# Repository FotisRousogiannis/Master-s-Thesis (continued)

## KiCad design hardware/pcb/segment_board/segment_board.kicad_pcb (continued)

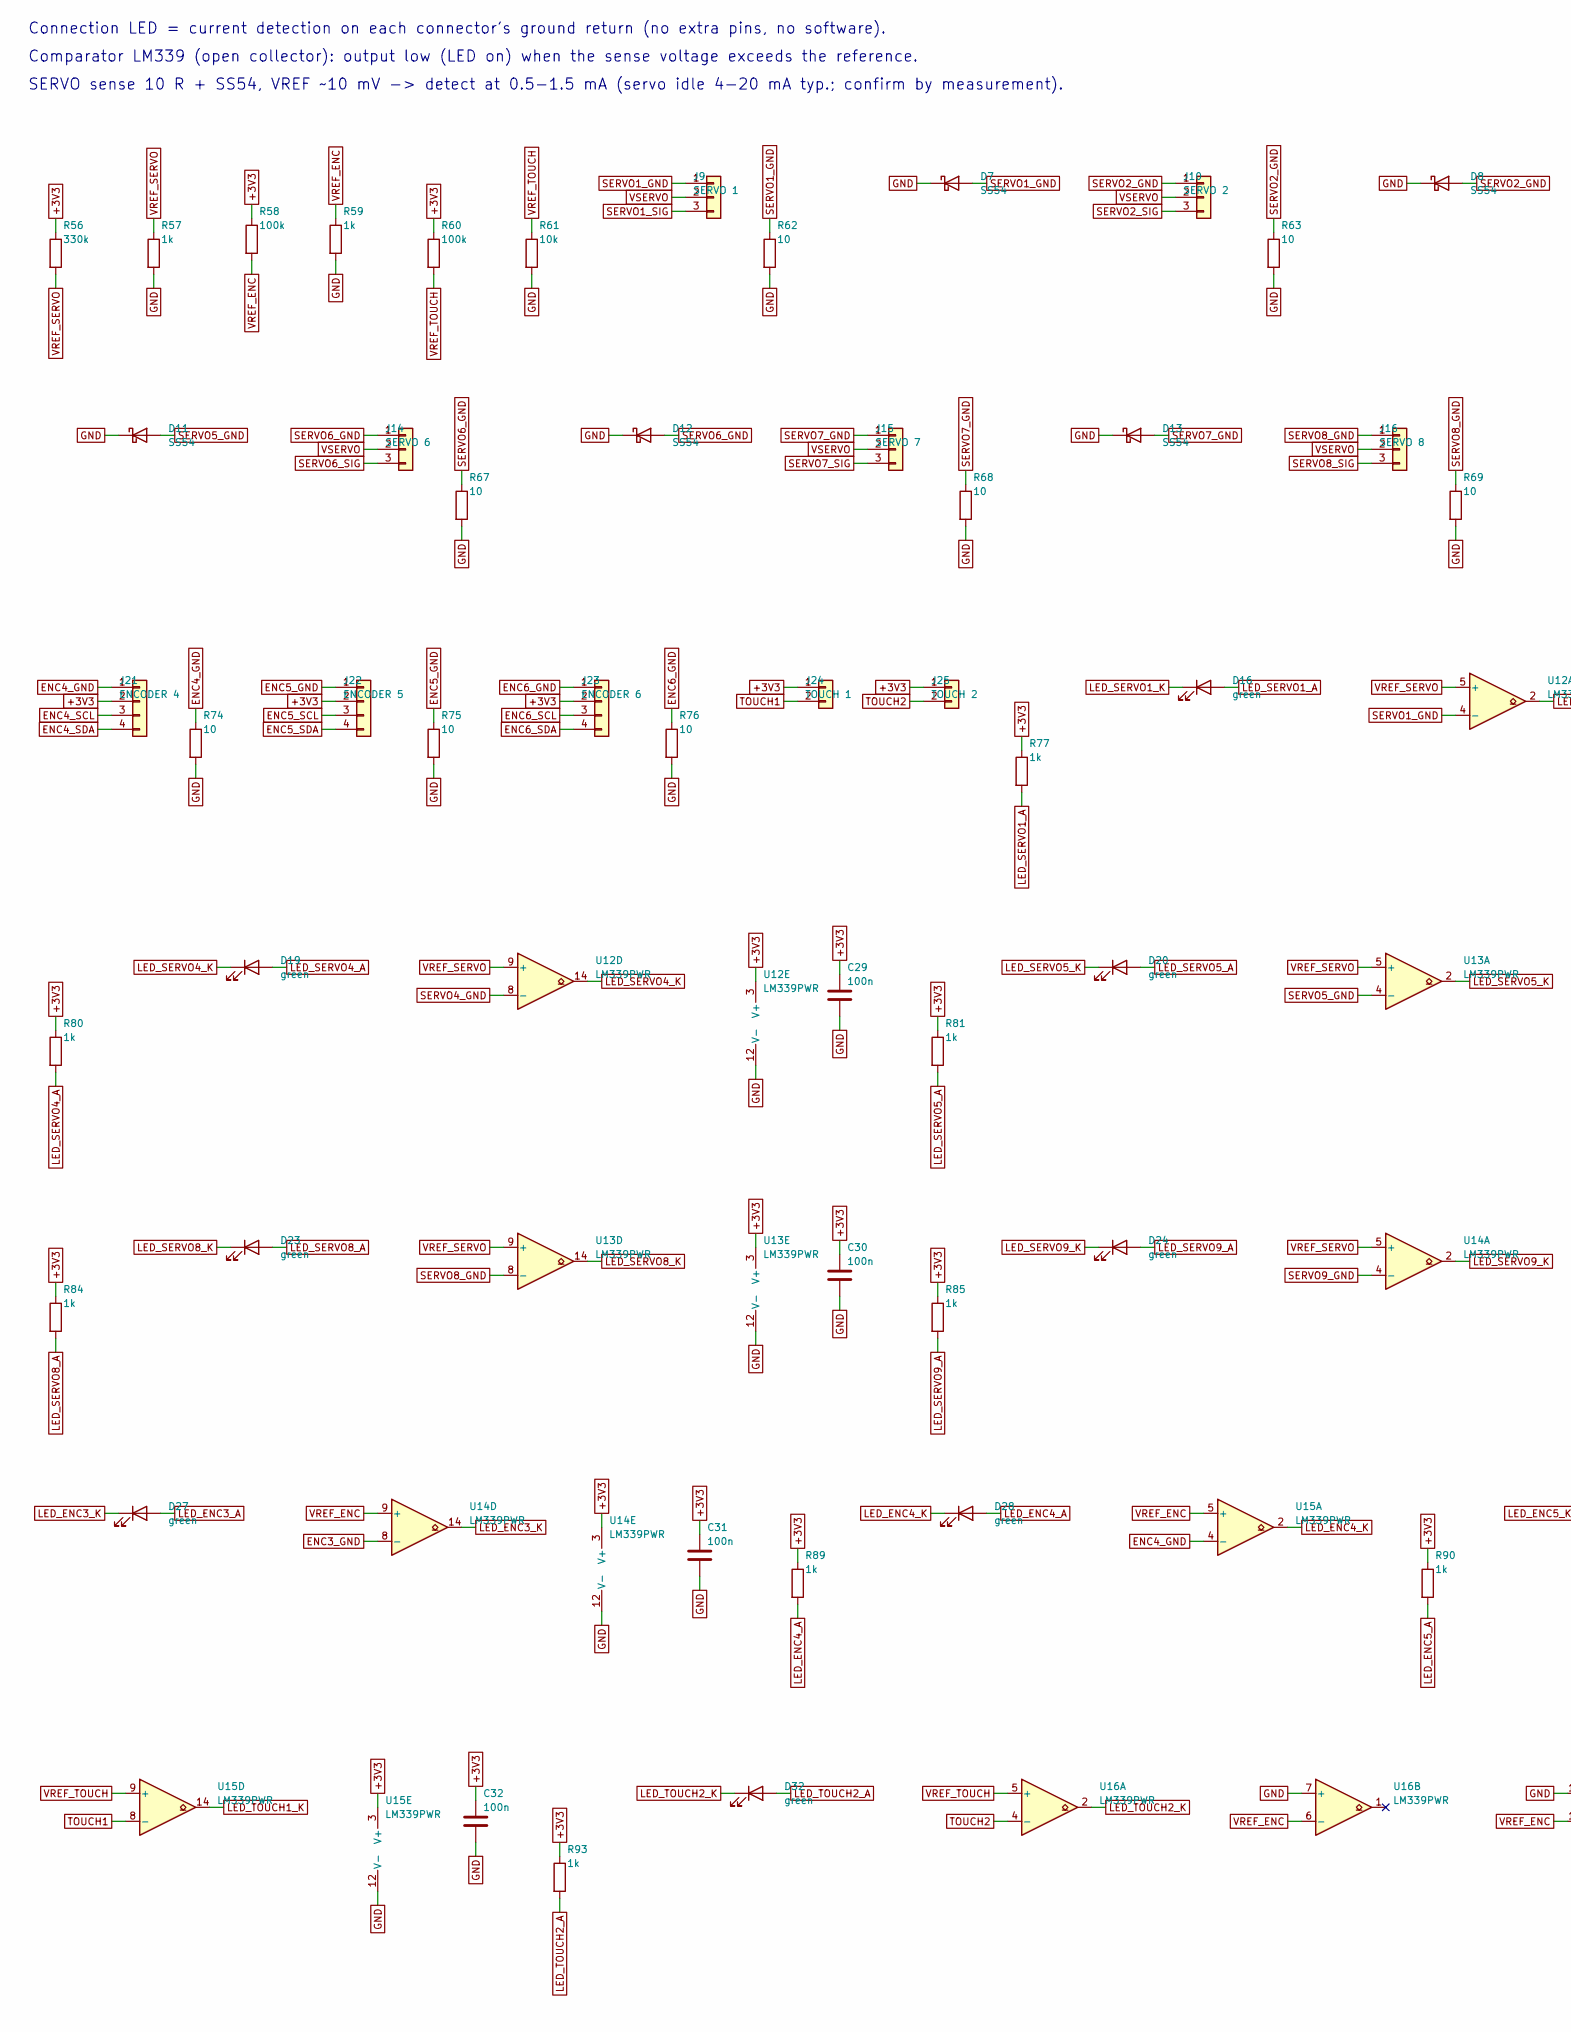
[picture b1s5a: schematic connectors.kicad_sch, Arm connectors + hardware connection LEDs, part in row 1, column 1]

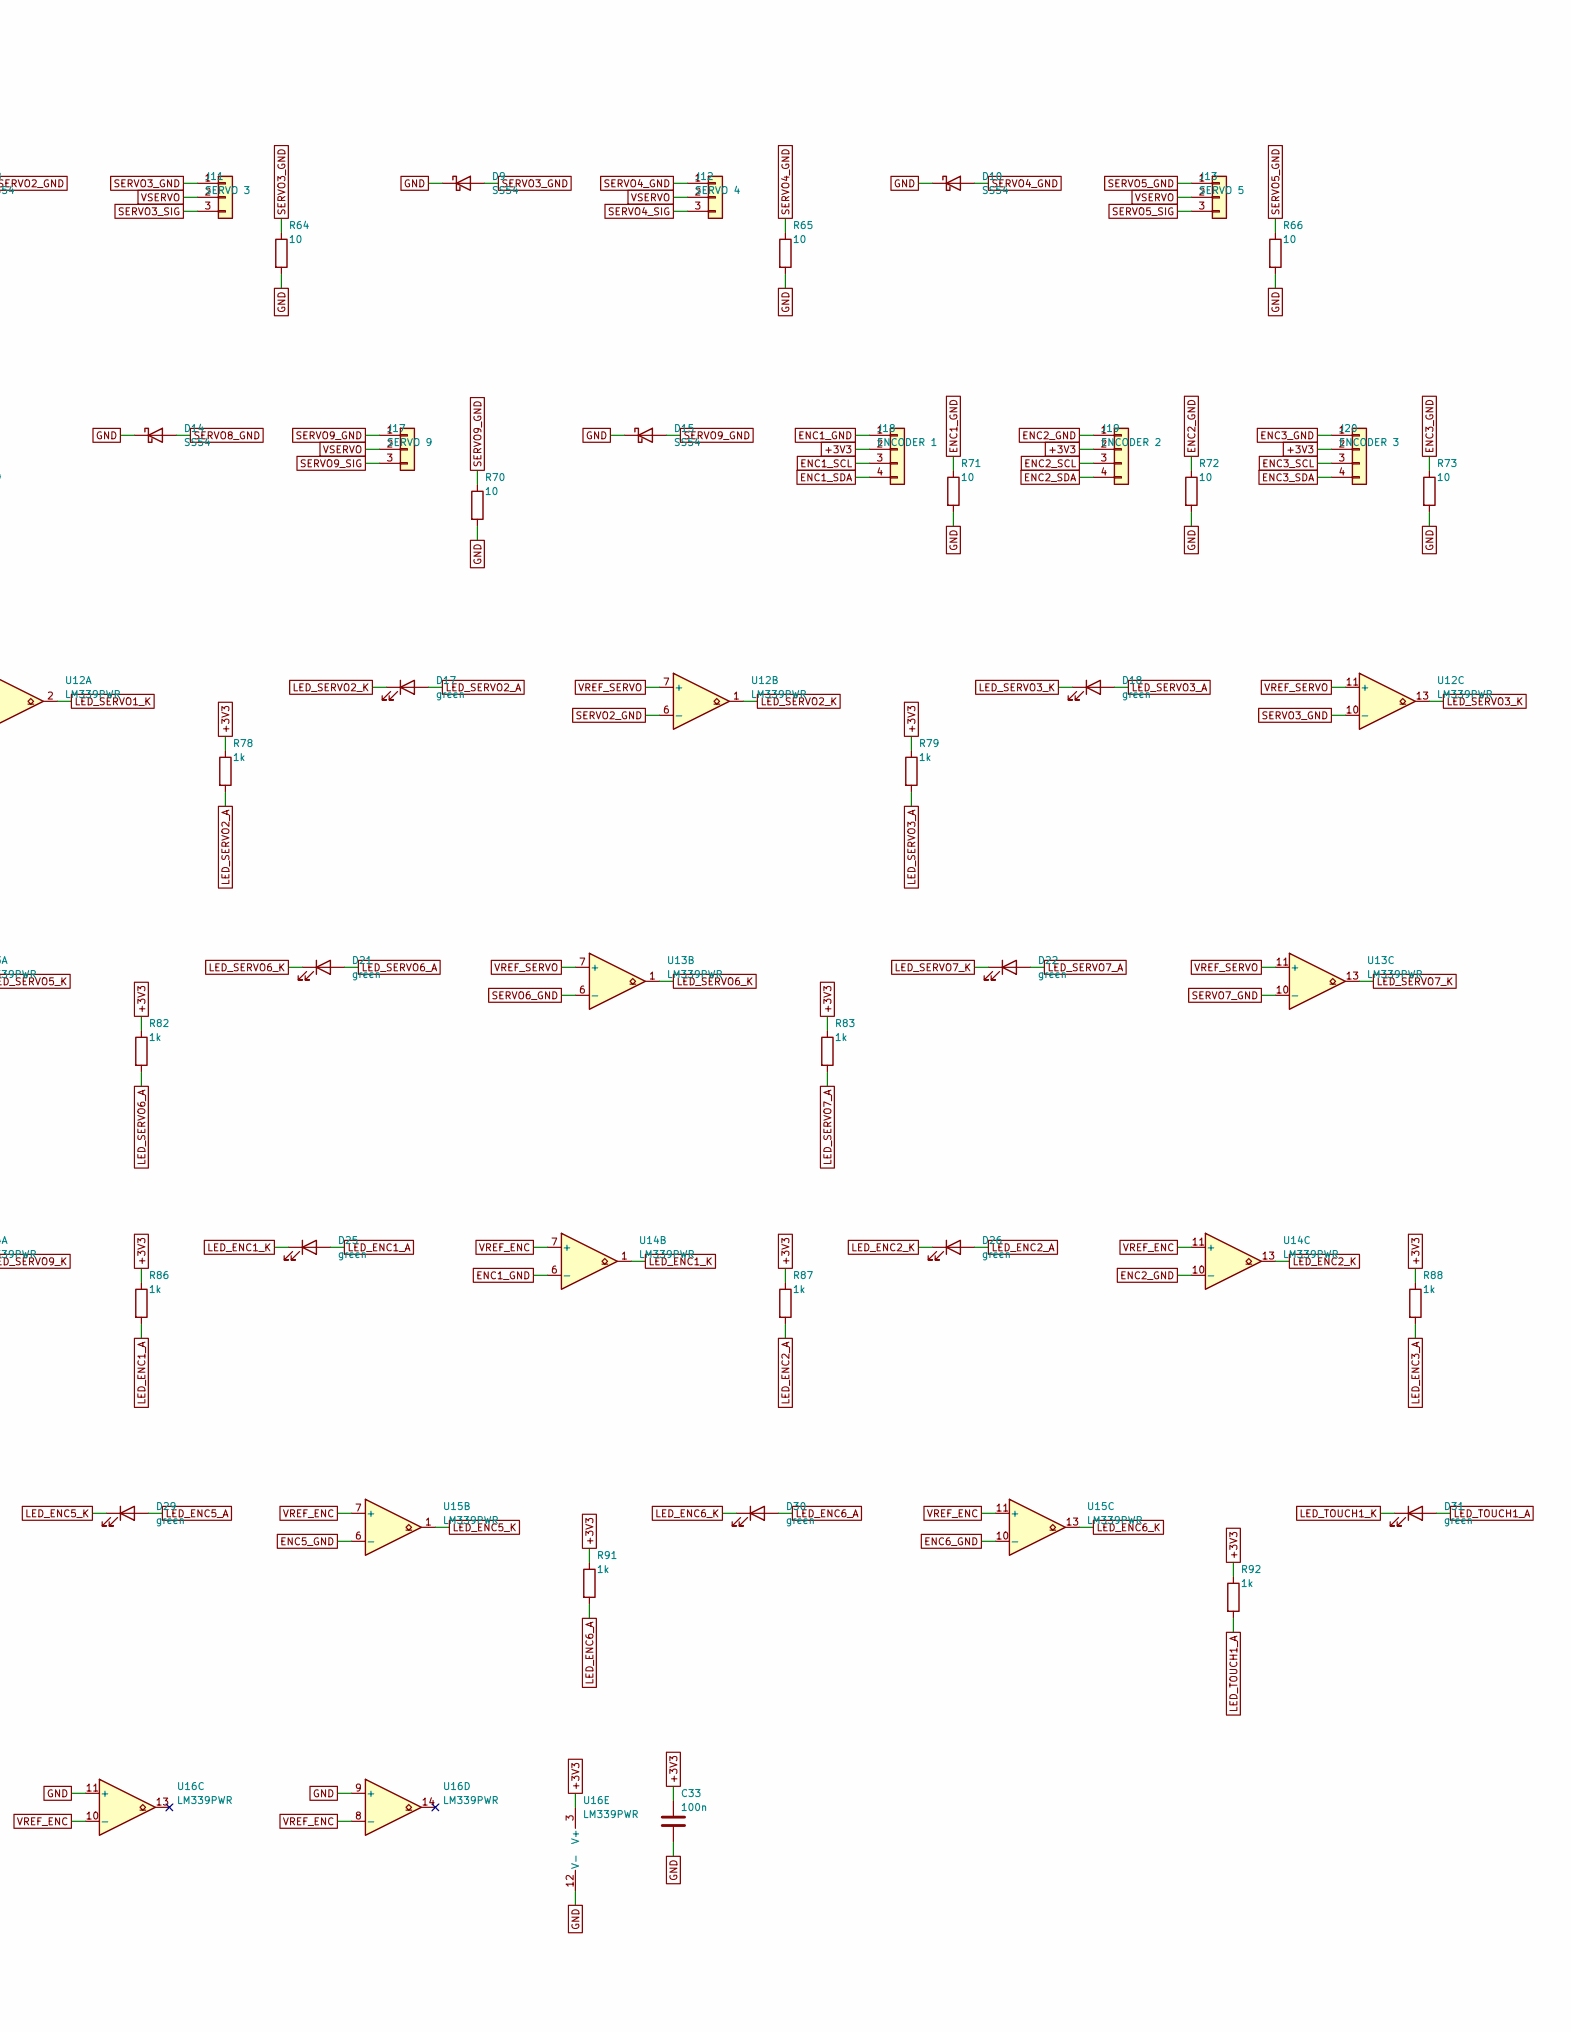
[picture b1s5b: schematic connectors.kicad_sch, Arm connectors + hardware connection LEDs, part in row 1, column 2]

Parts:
C29, C30, C31, C32, C33: 100n; C_0402_1005Metric; LCSC C1525
D7, D8, D9, D10, D11, D12, D13, D14, D15: SS54; D_SMA; LCSC C22452
D16, D17, D18, D19, D20, D21, D22, D23, D24, D25, D26, D27, D28, D29, D30, D31, D32: green; LED_0603_1608Metric; LCSC C2986030
J9: SERVO 1; PhoenixContact_MCV_1,5_3-G-3.5_1x03_P3.50mm_Vertical
J10: SERVO 2; PhoenixContact_MCV_1,5_3-G-3.5_1x03_P3.50mm_Vertical
J11: SERVO 3; PhoenixContact_MCV_1,5_3-G-3.5_1x03_P3.50mm_Vertical
J12: SERVO 4; PhoenixContact_MCV_1,5_3-G-3.5_1x03_P3.50mm_Vertical
J13: SERVO 5; PhoenixContact_MCV_1,5_3-G-3.5_1x03_P3.50mm_Vertical
J14: SERVO 6; PhoenixContact_MCV_1,5_3-G-3.5_1x03_P3.50mm_Vertical
J15: SERVO 7; PhoenixContact_MCV_1,5_3-G-3.5_1x03_P3.50mm_Vertical
J16: SERVO 8; PhoenixContact_MCV_1,5_3-G-3.5_1x03_P3.50mm_Vertical
J17: SERVO 9; PhoenixContact_MCV_1,5_3-G-3.5_1x03_P3.50mm_Vertical
J18: ENCODER 1; PhoenixContact_MCV_1,5_4-G-3.5_1x04_P3.50mm_Vertical
J19: ENCODER 2; PhoenixContact_MCV_1,5_4-G-3.5_1x04_P3.50mm_Vertical
J20: ENCODER 3; PhoenixContact_MCV_1,5_4-G-3.5_1x04_P3.50mm_Vertical
J21: ENCODER 4; PhoenixContact_MCV_1,5_4-G-3.5_1x04_P3.50mm_Vertical
J22: ENCODER 5; PhoenixContact_MCV_1,5_4-G-3.5_1x04_P3.50mm_Vertical
J23: ENCODER 6; PhoenixContact_MCV_1,5_4-G-3.5_1x04_P3.50mm_Vertical
J24: TOUCH 1; PhoenixContact_MCV_1,5_2-G-3.5_1x02_P3.50mm_Vertical
J25: TOUCH 2; PhoenixContact_MCV_1,5_2-G-3.5_1x02_P3.50mm_Vertical
R56: 330k; R_0402_1005Metric; LCSC C25778
R57, R59, R77, R78, R79, R80, R81, R82, R83, R84, R85, R86, R87, R88, R89, R90, R91, R92, R93: 1k; R_0402_1005Metric; LCSC C11702
R58, R60: 100k; R_0402_1005Metric; LCSC C25741
R61: 10k; R_0402_1005Metric; LCSC C25744
R62, R63, R64, R65, R66, R67, R68, R69, R70, R71, R72, R73, R74, R75, R76: 10; R_0402_1005Metric; LCSC C25077
U12, U13, U14, U15, U16: LM339PWR; TSSOP-14_4.4x5mm_P0.65mm; LCSC C42184

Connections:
+3V3: C29.1, C30.1, C31.1, C32.1, C33.1, J18.2, J19.2, J20.2, J21.2, J22.2, J23.2, J24.1, J25.1, R56.1, R58.1, R60.1, R77.1, R78.1, R79.1, R80.1, R81.1, R82.1, R83.1, R84.1, R85.1, R86.1, R87.1, R88.1, R89.1, R90.1, R91.1, R92.1, R93.1, U12.3 (V+), U13.3 (V+), U14.3 (V+), U15.3 (V+), U16.3 (V+); also elsewhere on the board
ENC1_GND: J18.1, R71.1, U14.6 (-)
ENC1_SCL: J18.3; also elsewhere on the board
ENC1_SDA: J18.4; also elsewhere on the board
ENC2_GND: J19.1, R72.1, U14.10 (-)
ENC2_SCL: J19.3; also elsewhere on the board
ENC2_SDA: J19.4; also elsewhere on the board
ENC3_GND: J20.1, R73.1, U14.8 (-)
ENC3_SCL: J20.3; also elsewhere on the board
ENC3_SDA: J20.4; also elsewhere on the board
ENC4_GND: J21.1, R74.1, U15.4 (-)
ENC4_SCL: J21.3; also elsewhere on the board
ENC4_SDA: J21.4; also elsewhere on the board
ENC5_GND: J22.1, R75.1, U15.6 (-)
ENC5_SCL: J22.3; also elsewhere on the board
ENC5_SDA: J22.4; also elsewhere on the board
ENC6_GND: J23.1, R76.1, U15.10 (-)
ENC6_SCL: J23.3; also elsewhere on the board
ENC6_SDA: J23.4; also elsewhere on the board
GND: C29.2, C30.2, C31.2, C32.2, C33.2, D7.1 (K), D8.1 (K), D9.1 (K), D10.1 (K), D11.1 (K), D12.1 (K), D13.1 (K), D14.1 (K), D15.1 (K), R57.2, R59.2, R61.2, R62.2, R63.2, R64.2, R65.2, R66.2, R67.2, R68.2, R69.2, R70.2, R71.2, R72.2, R73.2, R74.2, R75.2, R76.2, U12.12 (V-), U13.12 (V-), U14.12 (V-), U15.12 (V-), U16.7 (+), U16.9 (+), U16.11 (+), U16.12 (V-); also elsewhere on the board
LED_ENC1_A: D25.2 (A), R86.2
LED_ENC1_K: D25.1 (K), U14.1
LED_ENC2_A: D26.2 (A), R87.2
LED_ENC2_K: D26.1 (K), U14.13
LED_ENC3_A: D27.2 (A), R88.2
LED_ENC3_K: D27.1 (K), U14.14
LED_ENC4_A: D28.2 (A), R89.2
LED_ENC4_K: D28.1 (K), U15.2
LED_ENC5_A: D29.2 (A), R90.2
LED_ENC5_K: D29.1 (K), U15.1
LED_ENC6_A: D30.2 (A), R91.2
LED_ENC6_K: D30.1 (K), U15.13
LED_SERVO1_A: D16.2 (A), R77.2
LED_SERVO1_K: D16.1 (K), U12.2
LED_SERVO2_A: D17.2 (A), R78.2
LED_SERVO2_K: D17.1 (K), U12.1
LED_SERVO3_A: D18.2 (A), R79.2
LED_SERVO3_K: D18.1 (K), U12.13
LED_SERVO4_A: D19.2 (A), R80.2
LED_SERVO4_K: D19.1 (K), U12.14
LED_SERVO5_A: D20.2 (A), R81.2
LED_SERVO5_K: D20.1 (K), U13.2
LED_SERVO6_A: D21.2 (A), R82.2
LED_SERVO6_K: D21.1 (K), U13.1
LED_SERVO7_A: D22.2 (A), R83.2
LED_SERVO7_K: D22.1 (K), U13.13
LED_SERVO8_A: D23.2 (A), R84.2
LED_SERVO8_K: D23.1 (K), U13.14
LED_SERVO9_A: D24.2 (A), R85.2
LED_SERVO9_K: D24.1 (K), U14.2
LED_TOUCH1_A: D31.2 (A), R92.2
LED_TOUCH1_K: D31.1 (K), U15.14
LED_TOUCH2_A: D32.2 (A), R93.2
LED_TOUCH2_K: D32.1 (K), U16.2
SERVO1_GND: D7.2 (A), J9.1, R62.1, U12.4 (-)
SERVO1_SIG: J9.3; also elsewhere on the board
SERVO2_GND: D8.2 (A), J10.1, R63.1, U12.6 (-)
SERVO2_SIG: J10.3; also elsewhere on the board
SERVO3_GND: D9.2 (A), J11.1, R64.1, U12.10 (-)
SERVO3_SIG: J11.3; also elsewhere on the board
SERVO4_GND: D10.2 (A), J12.1, R65.1, U12.8 (-)
SERVO4_SIG: J12.3; also elsewhere on the board
SERVO5_GND: D11.2 (A), J13.1, R66.1, U13.4 (-)
SERVO5_SIG: J13.3; also elsewhere on the board
SERVO6_GND: D12.2 (A), J14.1, R67.1, U13.6 (-)
SERVO6_SIG: J14.3; also elsewhere on the board
SERVO7_GND: D13.2 (A), J15.1, R68.1, U13.10 (-)
SERVO7_SIG: J15.3; also elsewhere on the board
SERVO8_GND: D14.2 (A), J16.1, R69.1, U13.8 (-)
SERVO8_SIG: J16.3; also elsewhere on the board
SERVO9_GND: D15.2 (A), J17.1, R70.1, U14.4 (-)
SERVO9_SIG: J17.3; also elsewhere on the board
TOUCH1: J24.2, U15.8 (-); also elsewhere on the board
TOUCH2: J25.2, U16.4 (-); also elsewhere on the board
VREF_ENC: R58.2, R59.1, U14.7 (+), U14.9 (+), U14.11 (+), U15.5 (+), U15.7 (+), U15.11 (+), U16.6 (-), U16.8 (-), U16.10 (-)
VREF_SERVO: R56.2, R57.1, U12.5 (+), U12.7 (+), U12.9 (+), U12.11 (+), U13.5 (+), U13.7 (+), U13.9 (+), U13.11 (+), U14.5 (+)
VREF_TOUCH: R60.2, R61.1, U15.9 (+), U16.5 (+)
VSERVO: J9.2, J10.2, J11.2, J12.2, J13.2, J14.2, J15.2, J16.2, J17.2; also elsewhere on the board

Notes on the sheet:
Connection LED = current detection on each connector's ground return (no extra pins, no software).
Comparator LM339 (open collector): output low (LED on) when the sense voltage exceeds the reference.
SERVO sense 10 R + SS54, VREF ~10 mV -> detect at 0.5-1.5 mA (servo idle 4-20 mA typ.; confirm by measurement).

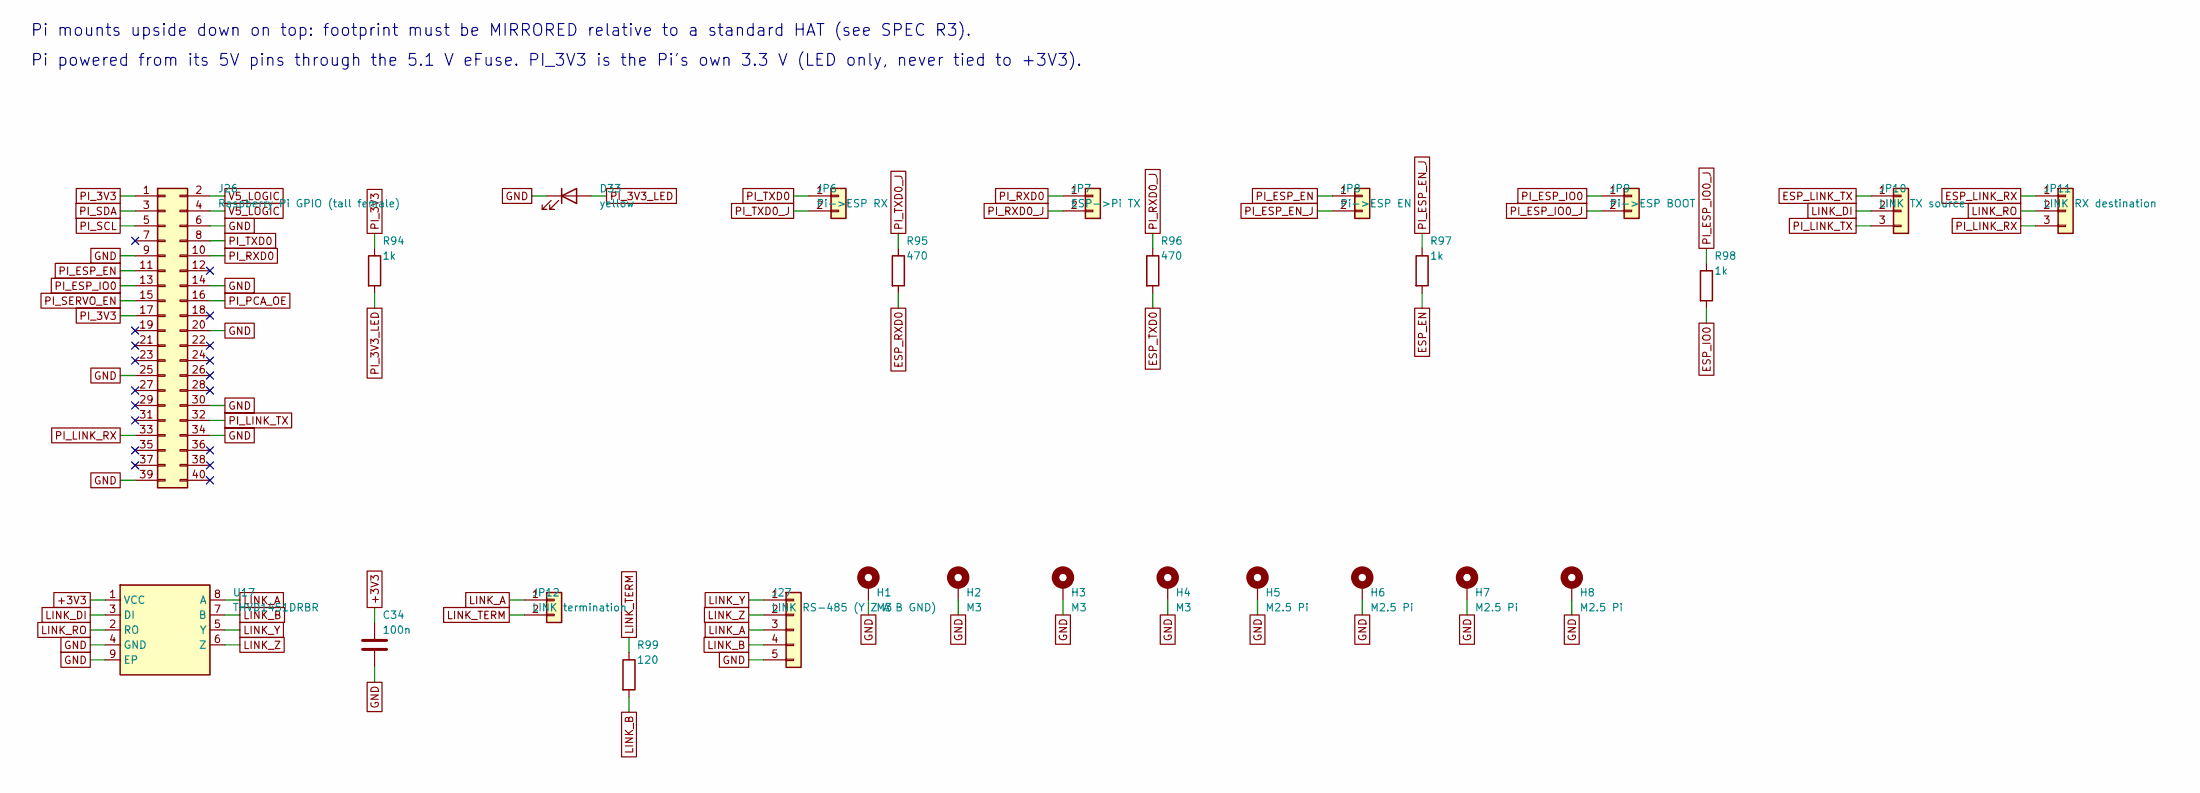
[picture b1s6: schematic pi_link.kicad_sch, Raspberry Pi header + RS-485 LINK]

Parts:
C34: 100n; C_0402_1005Metric; LCSC C1525
D33: yellow; LED_0603_1608Metric; LCSC C2986063
H1, H2, H3, H4: M3; MountingHole_3.2mm_M3_Pad_Via
H5, H6, H7, H8: M2.5 Pi; MountingHole_2.7mm_M2.5_Pad_Via
J26: Raspberry Pi GPIO (tall female); RPi_Socket_2x20_FaceDown
J27: LINK RS-485 (Y Z A B GND); PhoenixContact_MCV_1,5_5-G-3.5_1x05_P3.50mm_Vertical
JP6: Pi->ESP RX; PinHeader_1x02_P2.54mm_Vertical
JP7: ESP->Pi TX; PinHeader_1x02_P2.54mm_Vertical
JP8: Pi->ESP EN; PinHeader_1x02_P2.54mm_Vertical
JP9: Pi->ESP BOOT; PinHeader_1x02_P2.54mm_Vertical
JP10: LINK TX source; PinHeader_1x03_P2.54mm_Vertical
JP11: LINK RX destination; PinHeader_1x03_P2.54mm_Vertical
JP12: LINK termination; PinHeader_1x02_P2.54mm_Vertical
R94, R97, R98: 1k; R_0402_1005Metric; LCSC C11702
R95, R96: 470; R_0402_1005Metric; LCSC C25117
R99: 120; R_0402_1005Metric; LCSC C25079
U17: THVD1451DRBR; HVSON-8-1EP_3x3mm_P0.65mm_EP1.6x2.4mm; LCSC C2671344

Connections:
+3V3: C34.1, U17.1 (VCC); also elsewhere on the board
ESP_EN: R97.2; also elsewhere on the board
ESP_IO0: R98.2; also elsewhere on the board
ESP_LINK_RX: JP11.1; also elsewhere on the board
ESP_LINK_TX: JP10.1; also elsewhere on the board
ESP_RXD0: R95.2; also elsewhere on the board
ESP_TXD0: R96.2; also elsewhere on the board
GND: C34.2, D33.1 (K), H1.1 (1_1), H2.1 (1_1), H3.1 (1_1), H4.1 (1_1), H5.1 (1_1), H6.1 (1_1), H7.1 (1_1), H8.1 (1_1), J26.6, J26.9, J26.14, J26.20, J26.25, J26.30, J26.34, J26.39, J27.5, U17.4 (GND), U17.9 (EP); also elsewhere on the board
LINK_A: J27.3, JP12.1, U17.8 (A)
LINK_B: J27.4, R99.2, U17.7 (B)
LINK_DI: JP10.2, U17.3 (DI)
LINK_RO: JP11.2, U17.2 (RO)
LINK_TERM: JP12.2, R99.1
LINK_Y: J27.1, U17.5 (Y)
LINK_Z: J27.2, U17.6 (Z)
PI_3V3: J26.1, J26.17, R94.1
PI_3V3_LED: D33.2 (A), R94.2
PI_ESP_EN: J26.11, JP8.1
PI_ESP_EN_J: JP8.2, R97.1
PI_ESP_IO0: J26.13, JP9.1
PI_ESP_IO0_J: JP9.2, R98.1
PI_LINK_RX: J26.33, JP11.3
PI_LINK_TX: J26.32, JP10.3
PI_PCA_OE: J26.16; also elsewhere on the board
PI_RXD0: J26.10, JP7.1
PI_RXD0_J: JP7.2, R96.1
PI_SCL: J26.5; also elsewhere on the board
PI_SDA: J26.3; also elsewhere on the board
PI_SERVO_EN: J26.15; also elsewhere on the board
PI_TXD0: J26.8, JP6.1
PI_TXD0_J: JP6.2, R95.1
V5_LOGIC: J26.2, J26.4; also elsewhere on the board

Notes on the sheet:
Pi mounts upside down on top: footprint must be MIRRORED relative to a standard HAT (see SPEC R3).
Pi powered from its 5V pins through the 5.1 V eFuse. PI_3V3 is the Pi's own 3.3 V (LED only, never tied to +3V3).

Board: 4 copper layers, 235 parts (0 on the bottom side), 185 nets, no tracks yet.

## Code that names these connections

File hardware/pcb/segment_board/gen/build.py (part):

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def power_sheet():
    s = Sheet("power", "power.kicad_sch", "Power: inputs, protection, eFuses, 3.3 V")
    s.text("7.4 V SERVO: XT30 -> 15 A fuse -> P-MOSFET reverse polarity -> TVS -> eFuse TPS259827 (ILIM ~10 A, soft-start, EN) -> bulk caps -> INA219 shunt -> VSERVO. OUT to next board after the TVS (before the eFuse).")
    s.text("5.1 V LOGIC: MSTB -> TVS -> eFuse TPS259472A (ILM ~4.4 A, reverse blocking, OV clamp 5.7 V) -> V5_LOGIC (Pi 5V pins, 3.3 V buck). OUT to next board after the TVS.")
    s.text("E-STOP (board level): NC contact in series with the eFuse EN line; central E-stop cuts the 7.4 V line at the base (ADR-0015)")

    # 7.4 V servo input
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    R(s, "10k", "+3V3", "ESP_IO0")
    s.add(Part(ref("SW"), "Switch:SW_Push", "BOOT", {"1": "ESP_IO0", "2": "GND"}, FP["BTN"]))
    R(s, "1k", "STATUS_LED", "STATUS_LED_A")
    LED(s, "red", "STATUS_LED_A", "GND")   # low Vf: a blue LED (~3 V) stays dark on a 3.3 V GPIO
    # USB-C (device, USB 2.0)
    s.add(Part(ref("J"), "Connector:USB_C_Receptacle_USB2.0_16P", "USB-C",
               {"A1": "GND", "A12": "GND", "B1": "GND", "B12": "GND", "A4": "VBUS_USB", "A9": "VBUS_USB",
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                R(s, "1k", "+3V3", f"LED_{name}_A")
                LED(s, "green", f"LED_{name}_A", f"LED_{name}_K")
            else:
                nets = {out_pin: None, minus: "VREF_ENC", plus: "GND"}   # unused: output held off
            s.add(Part(cref, "Comparator:LM339", "LM339PWR", nets, "Package_SO:TSSOP-14_4.4x5mm_P0.65mm",
                       lcsc="C42184", unit=u + 1))
        s.add(Part(cref, "Comparator:LM339", "LM339PWR", {"3": "+3V3", "12": "GND"},
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def pi_link_sheet():
    s = Sheet("pi_link", "pi_link.kicad_sch", "Raspberry Pi header + RS-485 LINK")
    s.text("Pi mounts upside down on top: footprint must be MIRRORED relative to a standard HAT (see SPEC R3).")
    s.text("Pi powered from its 5V pins through the 5.1 V eFuse. PI_3V3 is the Pi's own 3.3 V (LED only, never tied to +3V3).")
    pi = {str(n): None for n in range(1, 41)}
    pi.update({"1": "PI_3V3", "17": "PI_3V3", "2": "V5_LOGIC", "4": "V5_LOGIC",
               "6": "GND", "9": "GND", "14": "GND", "20": "GND", "25": "GND", "30": "GND", "34": "GND", "39": "GND",
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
